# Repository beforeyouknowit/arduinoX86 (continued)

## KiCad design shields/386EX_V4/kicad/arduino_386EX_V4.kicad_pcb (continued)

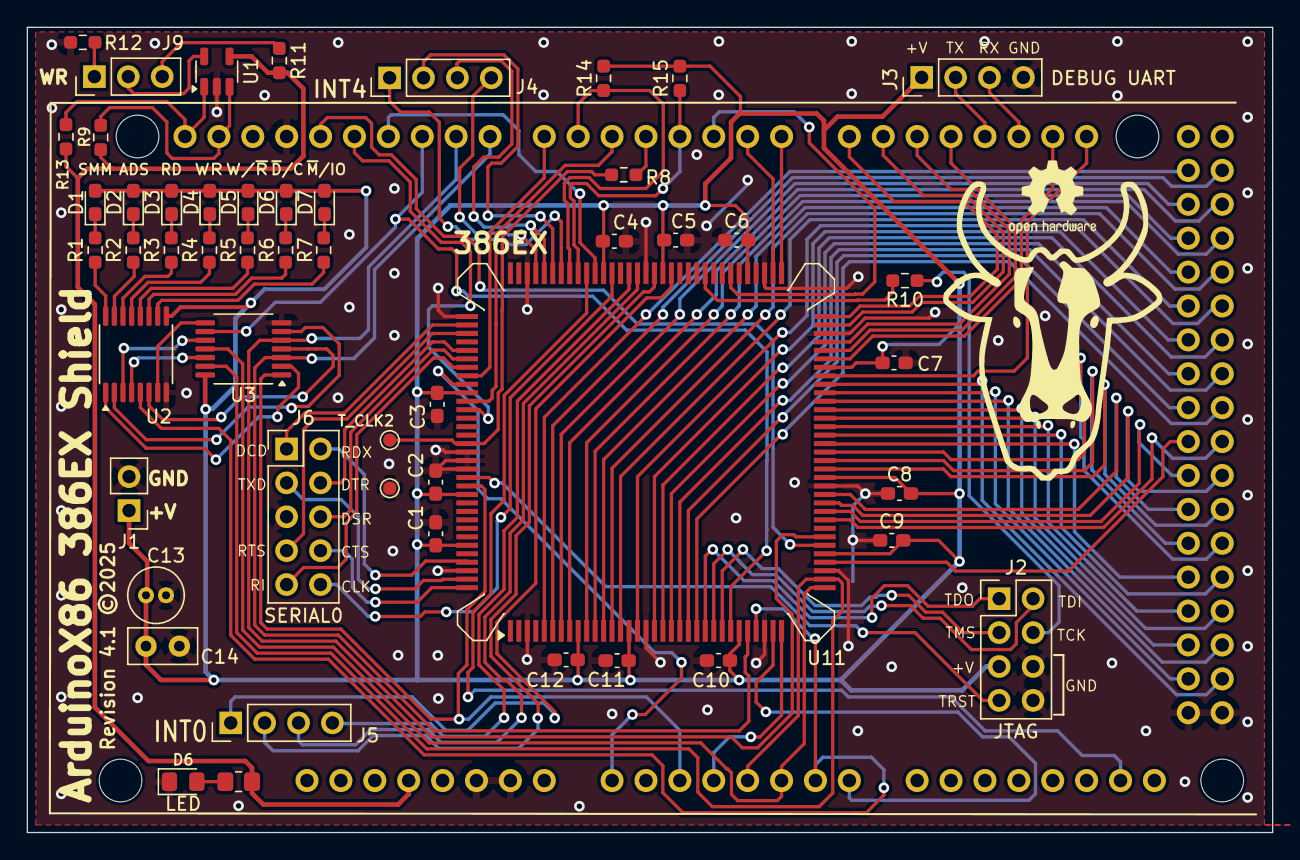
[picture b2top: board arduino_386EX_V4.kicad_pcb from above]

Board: 2 copper layers, 93.3 x 60.3 mm, 52 parts (0 on the bottom side), 115 nets.

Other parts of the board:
D6#2: LED; LED_0805_2012Metric_Pad1.15x1.40mm_HandSolder
R6#2: R_Small; R_0603_1608Metric_Pad0.98x0.95mm_HandSolder
R9, R13, R14, R15: R; R_0603_1608Metric_Pad0.98x0.95mm_HandSolder

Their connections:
GND: D6#2.1 (K); also elsewhere on the board
SCL: R13.1; also elsewhere on the board
SDA: R9.1; also elsewhere on the board
~BUSY: R14.1; also elsewhere on the board
~ERROR: R15.1; also elsewhere on the board

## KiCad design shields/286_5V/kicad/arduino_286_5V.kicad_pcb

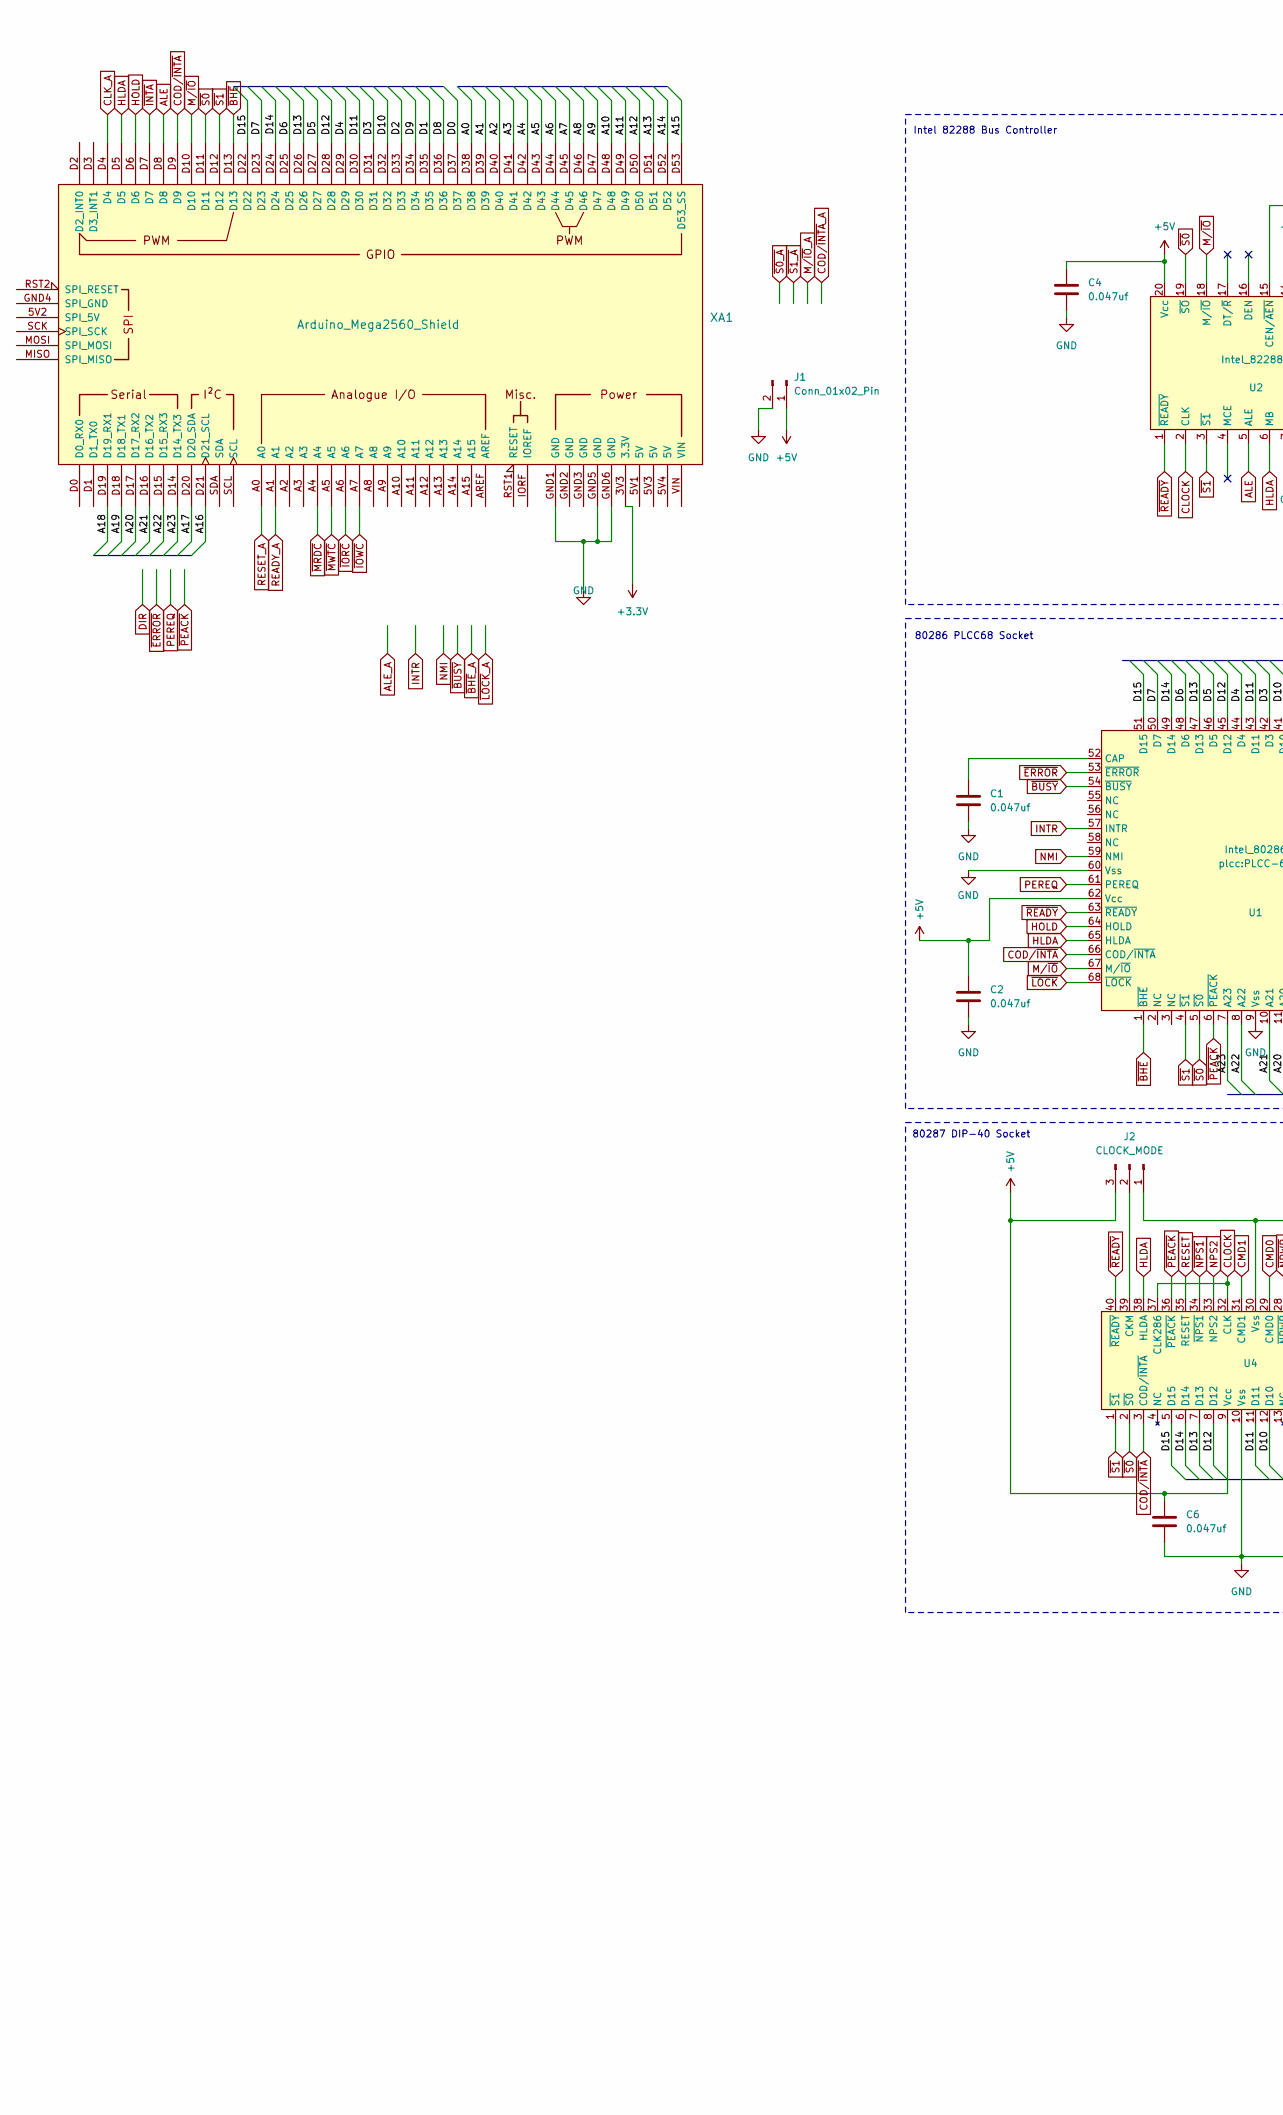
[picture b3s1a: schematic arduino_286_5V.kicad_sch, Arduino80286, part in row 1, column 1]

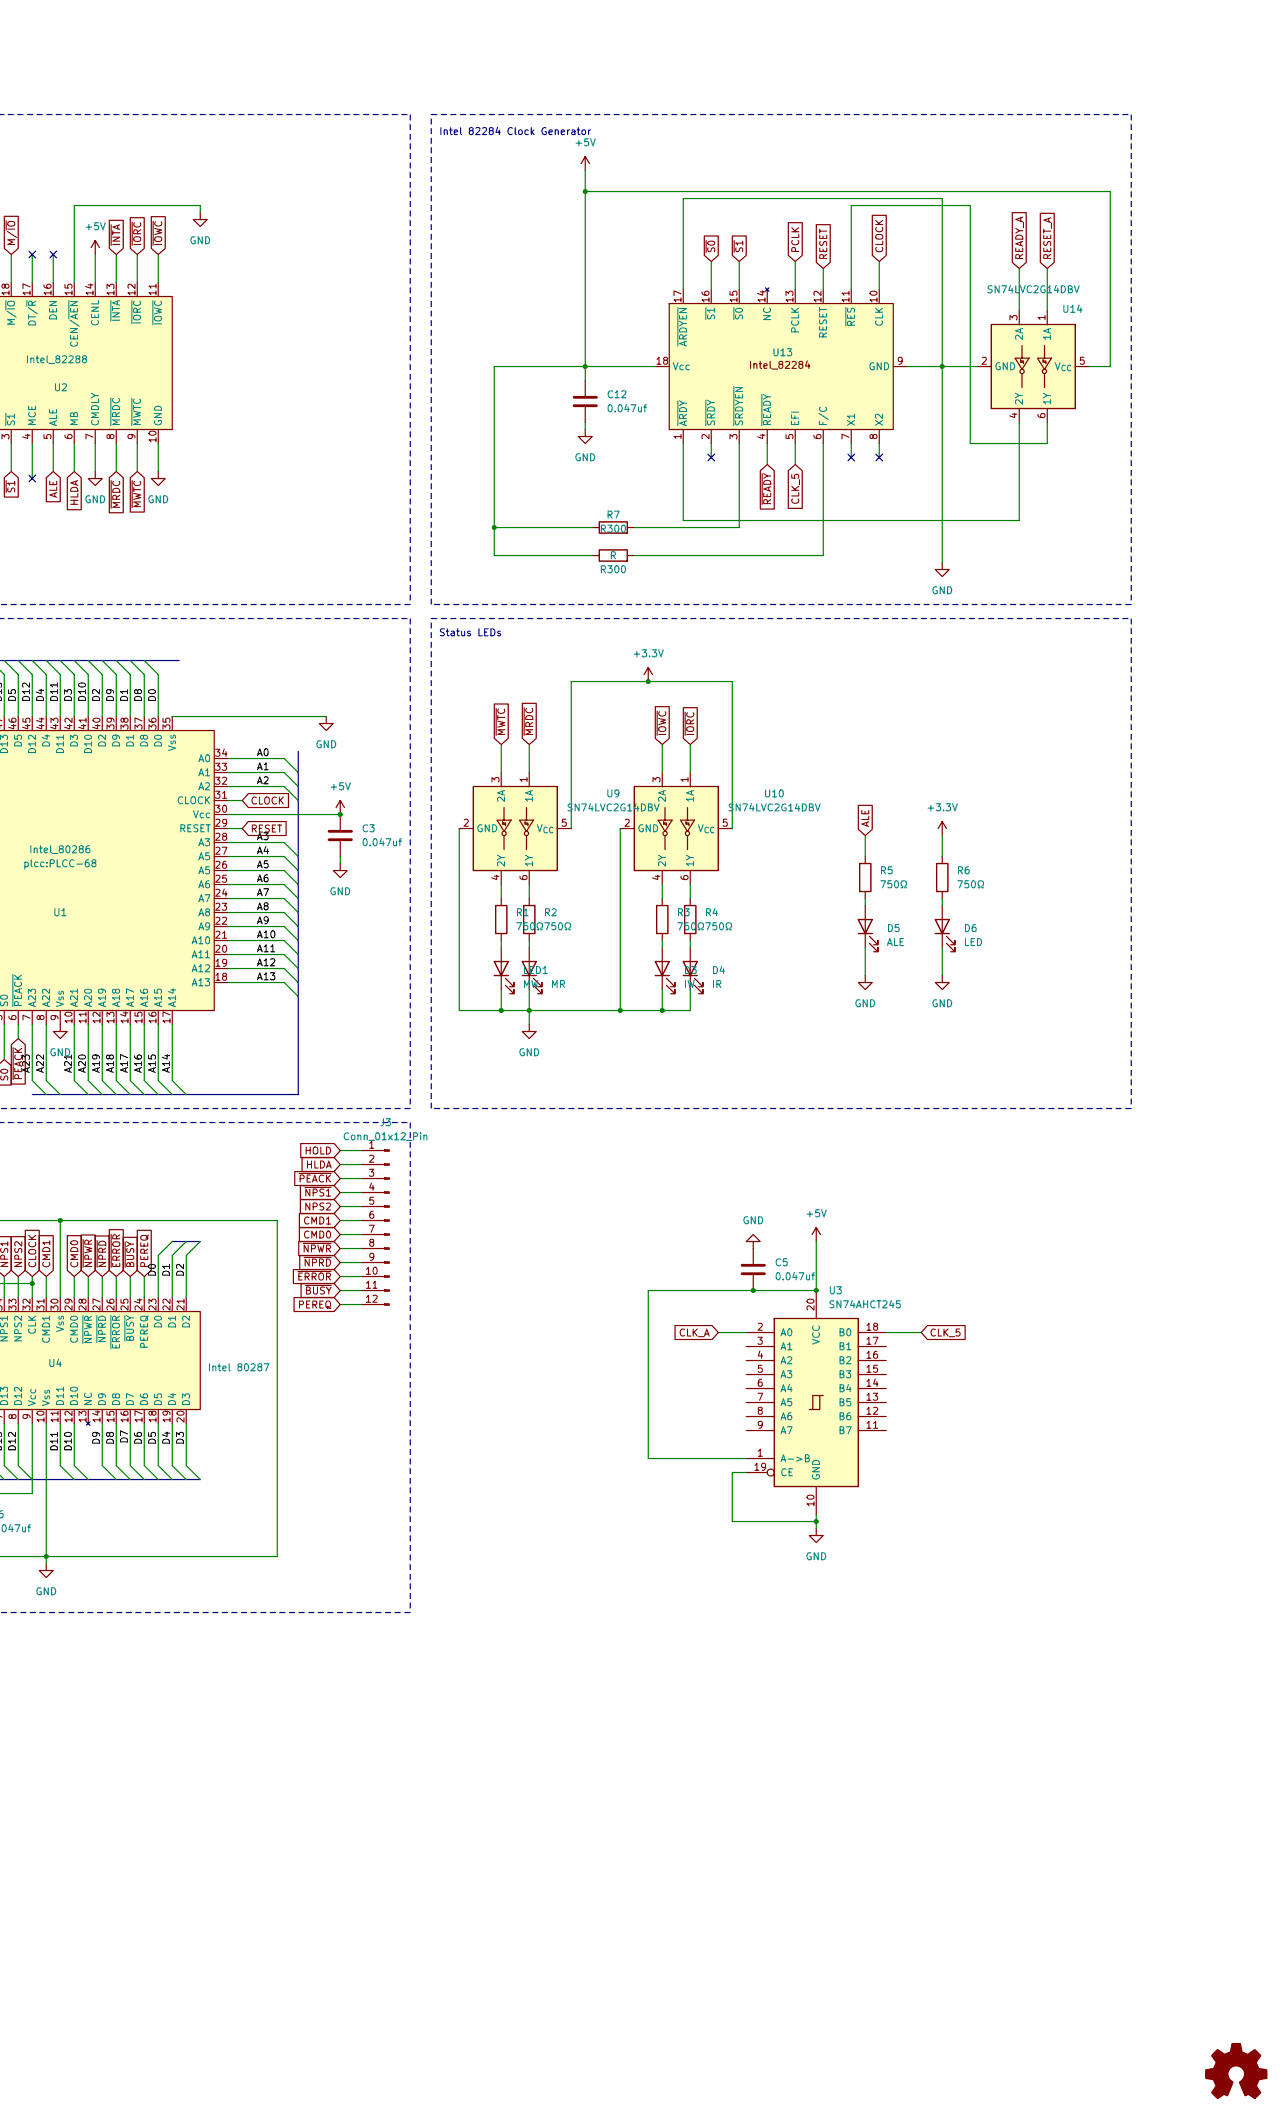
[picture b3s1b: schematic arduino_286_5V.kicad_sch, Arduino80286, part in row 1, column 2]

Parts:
C1, C2, C3, C4, C5, C6, C12: 0.047uf; C_0603_1608Metric_Pad1.08x0.95mm_HandSolder
D3: IW; LED_0805_2012Metric_Pad1.15x1.40mm_HandSolder
D4: IR; LED_0805_2012Metric_Pad1.15x1.40mm_HandSolder
D5: ALE; LED_0805_2012Metric_Pad1.15x1.40mm_HandSolder
D6: LED; LED_0805_2012Metric_Pad1.15x1.40mm_HandSolder
J1: Conn_01x02_Pin; PinHeader_1x02_P2.54mm_Horizontal
J2: CLOCK_MODE; PinHeader_1x03_P2.54mm_Vertical
J3: Conn_01x12_Pin; PinHeader_1x12_P2.54mm_Vertical
LED1: MW; LED_0805_2012Metric_Pad1.15x1.40mm_HandSolder
LED2: MR; LED_0805_2012Metric_Pad1.15x1.40mm_HandSolder
R1, R2, R3, R4, R5, R6: 750Ω; R_0805_2012Metric_Pad1.20x1.40mm_HandSolder
R7: R300; R_0805_2012Metric_Pad1.20x1.40mm_HandSolder
R300: R; R_0805_2012Metric_Pad1.20x1.40mm_HandSolder
U1: Intel_80286; PLCC-68
U2: Intel_82288; DIP-20_W7.62mm_Socket
U3: SN74AHCT245; TSSOP-20_4.4x6.5mm_P0.65mm
U4: Intel 80287; DIP-40_W15.24mm_Socket
U9, U10, U14: SN74LVC2G14DBV; SOT-23-6
U13: DIP-18_W7.62mm_Socket
XA1: Arduino_Mega2560_Shield

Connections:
+3.3V: R6.1, U9.5 (V_{CC}), U10.5 (V_{CC}), XA1.3V3 (3.3V)
+5V: C2.2, C3.2, C4.2, C5.2, C6.2, C12.2, J1.1, J2.3, R7.1, R300.1, U1.30 (Vcc), U1.62 (Vcc), U2.14 (CENL), U2.20 (Vcc), U3.1 (A->B), U3.20 (VCC), U4.9 (Vcc), U13.18 (Vcc), U14.5 (V_{CC})
/A0: U1.34 (A0), XA1.D38
/A1: U1.33 (A1), XA1.D39
/A2: U1.32 (A2), XA1.D40
/A3: U1.28 (A3), XA1.D41
/A4: U1.27 (A5), XA1.D42
/A5: U1.26 (A5), XA1.D43
/A6: U1.25 (A6), XA1.D44
/A7: U1.24 (A7), XA1.D45
/A8: U1.23 (A8), XA1.D46
/A9: U1.22 (A9), XA1.D47
/A10: U1.21 (A10), XA1.D48
/A11: U1.20 (A11), XA1.D49
/A12: U1.19 (A12), XA1.D50
/A13: U1.18 (A13), XA1.D51
/A14: U1.17 (A14), XA1.D52
/A15: U1.16 (A15), XA1.D53 (D53_SS)
/A16: U1.15 (A16), XA1.D21 (D21_SCL)
/A17: U1.14 (A17), XA1.D20 (D20_SDA)
/A18: U1.13 (A18), XA1.D19 (D19_RX1)
/A19: U1.12 (A19), XA1.D18 (D18_TX1)
/A20: U1.11 (A20), XA1.D17 (D17_RX2)
/A21: U1.10 (A21), XA1.D16 (D16_TX2)
/A22: U1.8 (A22), XA1.D15 (D15_RX3)
/A23: U1.7 (A23), XA1.D14 (D14_TX3)
/D0: U1.36 (D0), U4.23 (D0), XA1.D37
/D1: U1.38 (D1), U4.22 (D1), XA1.D35
/D2: U1.40 (D2), U4.21 (D2), XA1.D33
/D3: U1.42 (D3), U4.20 (D3), XA1.D31
/D4: U1.44 (D4), U4.19 (D4), XA1.D29
/D5: U1.46 (D5), U4.18 (D5), XA1.D27
/D6: U1.48 (D6), U4.17 (D6), XA1.D25
/D7: U1.50 (D7), U4.16 (D7), XA1.D23
/D8: U1.37 (D8), U4.15 (D8), XA1.D36
/D9: U1.39 (D9), U4.14 (D9), XA1.D34
/D10: U1.41 (D10), U4.12 (D10), XA1.D32
/D11: U1.43 (D11), U4.11 (D11), XA1.D30
/D12: U1.45 (D12), U4.8 (D12), XA1.D28
/D13: U1.47 (D13), U4.7 (D13), XA1.D26
/D14: U1.49 (D14), U4.6 (D14), XA1.D24
/D15: U1.51 (D15), U4.5 (D15), XA1.D22
ALE: R5.1, U2.5 (ALE), XA1.D8
CLK_5: U3.18 (B0), U13.5 (EFI)
CLK_A: U3.2 (A0), XA1.D4
CLOCK: U1.31 (CLOCK), U2.2 (CLK), U4.32 (CLK), U4.37 (CLK286), U13.10 (CLK)
CMD0: J3.7, U4.29 (CMD0)
CMD1: J3.6, U4.31 (CMD1)
COD/~INTA: U1.66 (COD/~INTA), U4.3 (COD/~INTA), XA1.D9
GND: C1.1, C2.1, C3.1, C4.1, C5.1, C6.1, C12.1, D3.1 (K), D4.1 (K), D5.1 (K), D6.1 (K), J1.2, J2.1, LED1.1 (K), LED2.1 (K), U1.9 (Vss), U1.35 (Vss), U1.60 (Vss), U2.7 (CMDLY), U2.10 (GND), U2.15 (CEN/~AEN), U3.10 (GND), U3.19 (CE), U4.10 (Vss), U4.30 (Vss), U9.2 (GND), U10.2 (GND), U13.9 (GND), U13.17 (~ARDYEN), U14.2 (GND), XA1.GND1 (GND), XA1.GND2 (GND), XA1.GND3 (GND), XA1.GND5 (GND), XA1.GND6 (GND)
HLDA: J3.2, U1.65 (HLDA), U2.6 (MB), U4.38 (HLDA), XA1.D5
HOLD: J3.1, U1.64 (HOLD), XA1.D6
INTR: U1.57 (INTR)
M/~IO: U1.67 (M/~IO), U2.18 (M/~IO), XA1.D10
NMI: U1.59 (NMI)
NPS2: J3.5, U4.33 (NPS2)
unnamed: D3.2 (A), R3.2
unnamed: D4.2 (A), R4.2
unnamed: D5.2 (A), R5.2
unnamed: D6.2 (A), R6.2
unnamed: J2.2, U4.39 (CKM)
unnamed: LED1.2 (A), R1.2
unnamed: LED2.2 (A), R2.2
unnamed: C1.2, U1.52 (CAP)
unnamed: R2.1, U9.6 (1Y)
unnamed: R1.1, U9.4 (2Y)
unnamed: R4.1, U10.6 (1Y)
unnamed: R3.1, U10.4 (2Y)
unnamed: R300.2, U13.6 (F/C)
unnamed: U13.1 (~ARDY), U14.4 (2Y)
unnamed: U13.11 (~RES), U14.6 (1Y)
unnamed: R7.2, U13.3 (~SRDYEN)
PCLK: U13.13 (PCLK)
PEREQ: J3.12, U1.61 (PEREQ), U4.24 (PEREQ)
READY_A: U14.3 (2A), XA1.A1
RESET: U1.29 (RESET), U4.35 (RESET), U13.12 (RESET)
RESET_A: U14.1 (1A), XA1.A0
~BHE: U1.1 (~BHE), XA1.D13
~BUSY: J3.11, U1.54 (~BUSY), U4.25 (~BUSY)
~ERROR: J3.10, U1.53 (~ERROR), U4.26 (~ERROR)
~INTA: U2.13 (~INTA), XA1.D7
~IORC: U2.12 (~IORC), U10.1 (1A), XA1.A6
~IOWC: U2.11 (~IOWC), U10.3 (2A), XA1.A7
~LOCK: U1.68 (~LOCK)
~MRDC: U2.8 (~MRDC), U9.1 (1A), XA1.A4
~MWTC: U2.9 (~MWTC), U9.3 (2A), XA1.A5
~NPRD: J3.9, U4.27 (~NPRD)
~NPS1: J3.4, U4.34 (~NPS1)
~NPWR: J3.8, U4.28 (~NPWR)
~PEACK: J3.3, U1.6 (~PEACK), U4.36 (~PEACK)
~READY: U1.63 (~READY), U2.1 (~READY), U4.40 (~READY), U13.4 (~READY)
~S0: U1.5 (~S0), U2.19 (~SO), U4.2 (~S0), U13.16 (~S1), XA1.D11
~S1: U1.4 (~S1), U2.3 (~S1), U4.1 (~S1), U13.15 (~S0), XA1.D12

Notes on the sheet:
Intel 82284 Clock Generator
Intel 82288 Bus Controller
80286 PLCC68 Socket
80287 DIP-40 Socket
Status LEDs

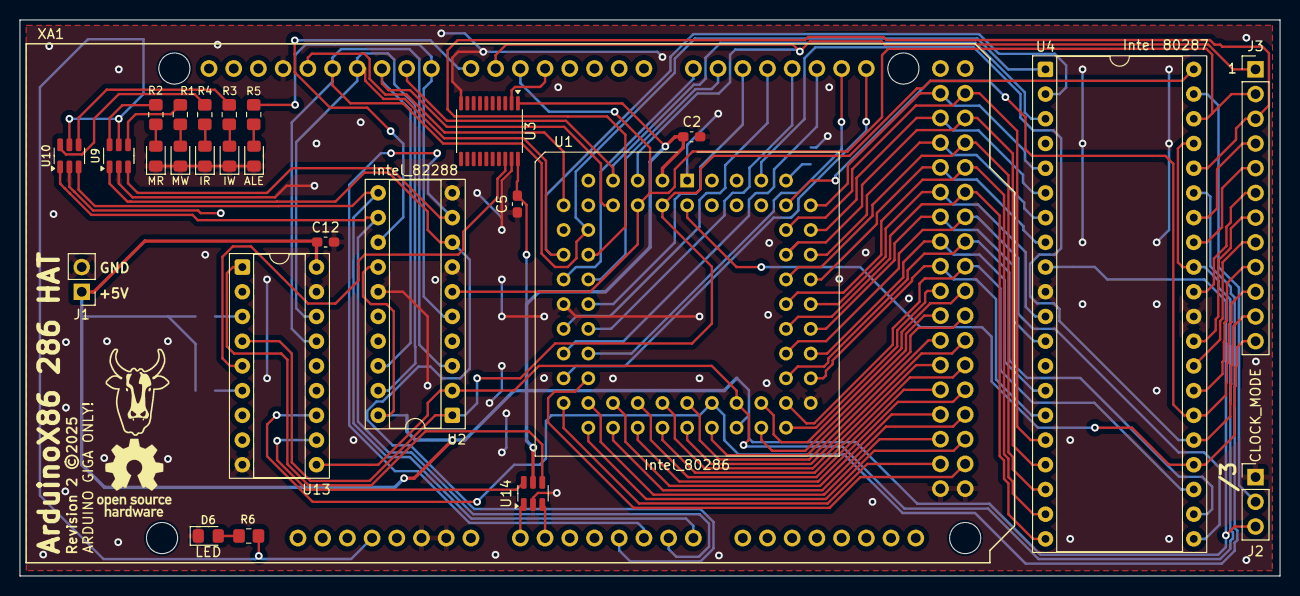
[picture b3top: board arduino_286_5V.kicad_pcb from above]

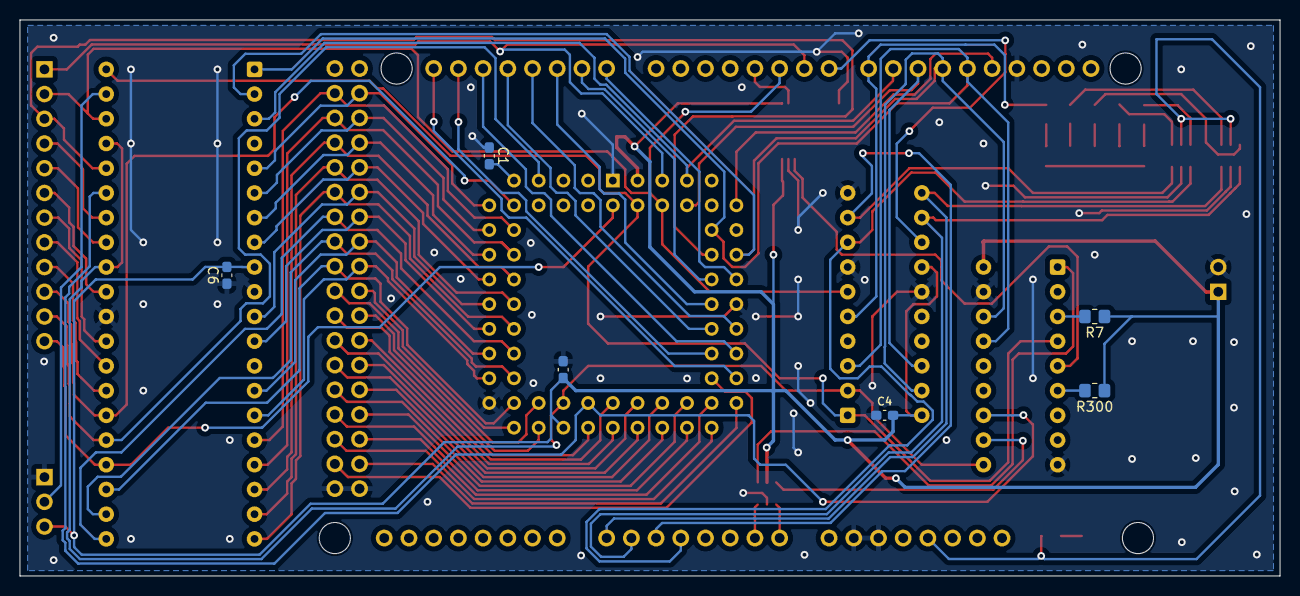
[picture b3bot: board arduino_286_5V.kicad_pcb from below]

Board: 2 copper layers, 129.5 x 57.1 mm, 33 parts (6 on the bottom side), 89 nets.

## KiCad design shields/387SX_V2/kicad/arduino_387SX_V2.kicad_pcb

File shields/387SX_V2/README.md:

## ArduinoX86 387SX Shield

This is a shield for the 387SX FPU. It is designed to be stacked on top of the 386EX V4 board.

## BOM

- This board has not been ordered and tested. I do not recommend being the first to do so!
- TBD

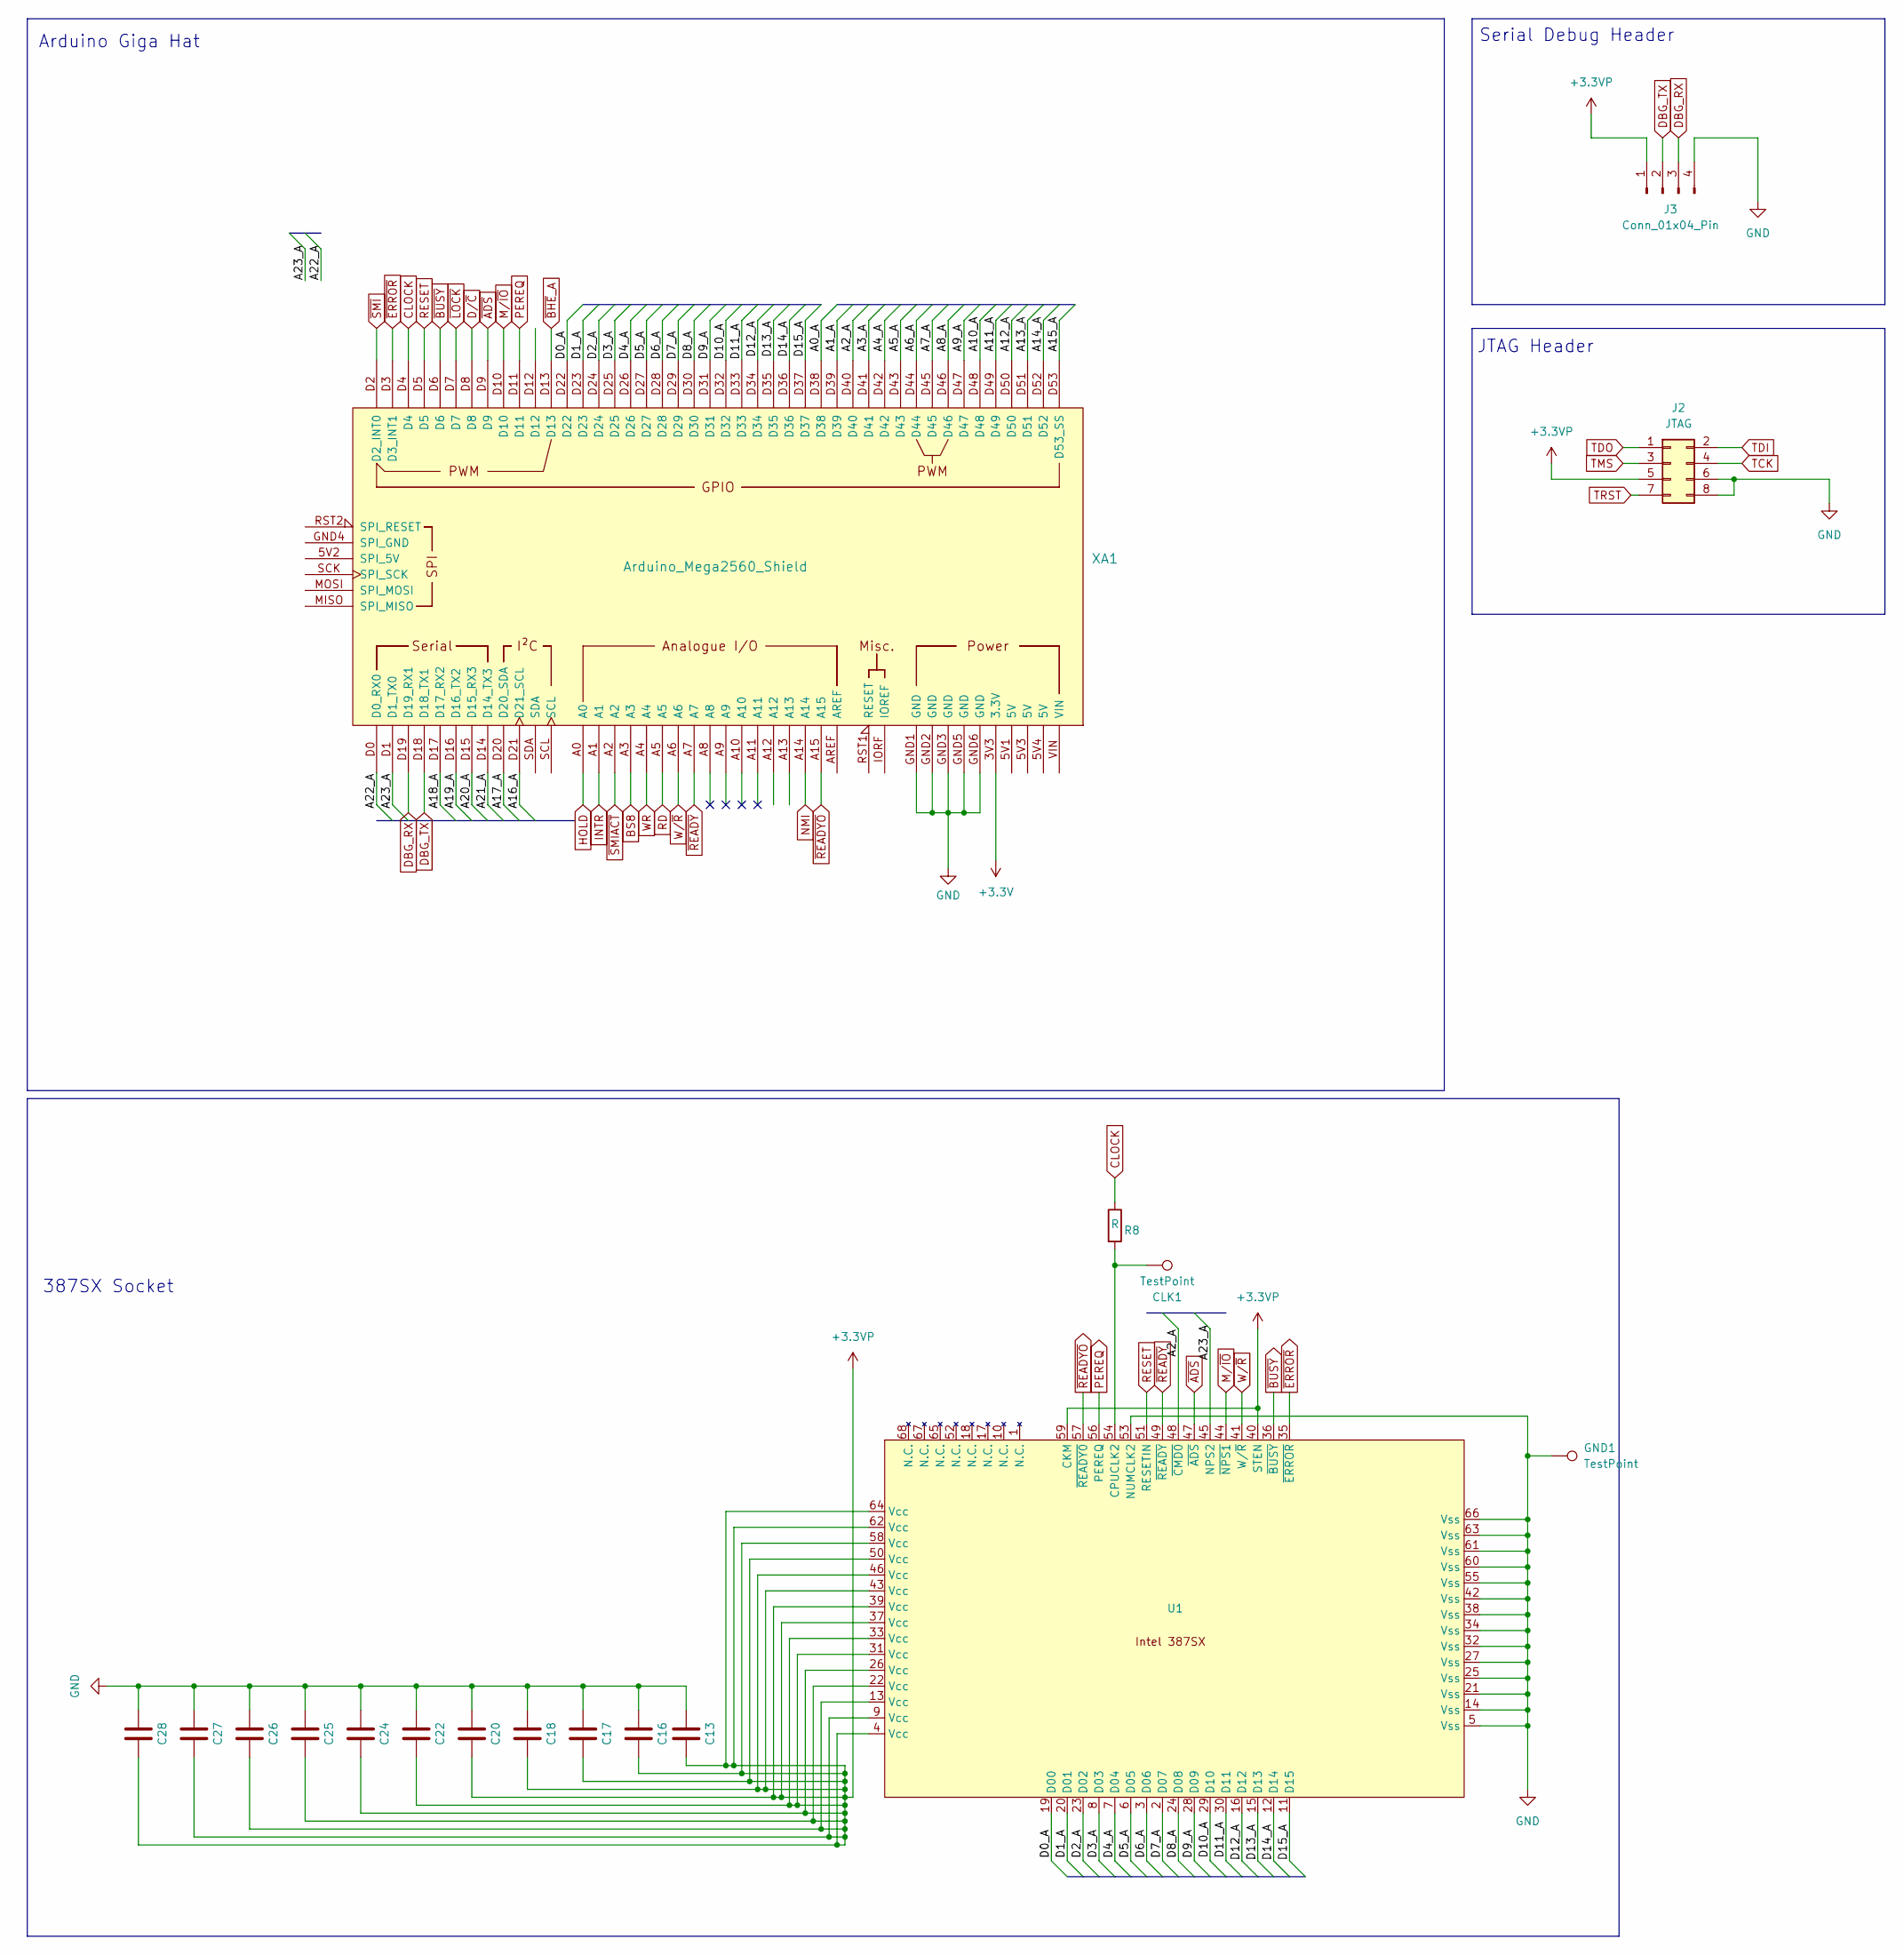
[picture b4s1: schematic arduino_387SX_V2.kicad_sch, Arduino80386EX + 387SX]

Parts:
C13, C16, C17, C18, C20, C22, C24, C25, C26, C27, C28: C; C_0603_1608Metric_Pad1.08x0.95mm_HandSolder
CLK1: TestPoint; TestPoint_Pad_D1.0mm
GND1: TestPoint; TestPoint_Pad_D1.0mm
J2: JTAG; PinSocket_2x04_P2.54mm_Vertical
J3: Conn_01x04_Pin; PinHeader_1x04_P2.54mm_Vertical
R8: R; R_0603_1608Metric_Pad0.98x0.95mm_HandSolder
U1: PLCC-68_286-THT-Socket
XA1: Arduino_Mega2560_Shield

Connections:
+3.3V: XA1.3V3 (3.3V)
+3.3VP: C13.2, C16.2, C17.2, C18.2, C20.2, C22.2, C24.2, C25.2, C26.2, C27.2, C28.2, J2.5, J3.1, U1.4 (Vcc), U1.9 (Vcc), U1.13 (Vcc), U1.22 (Vcc), U1.26 (Vcc), U1.31 (Vcc), U1.33 (Vcc), U1.37 (Vcc), U1.39 (Vcc), U1.40 (STEN), U1.43 (Vcc), U1.46 (Vcc), U1.50 (Vcc), U1.58 (Vcc), U1.59 (CKM), U1.62 (Vcc), U1.64 (Vcc)
/A0_A: XA1.D38
/A1_A: XA1.D39
/A2_A: U1.48 (~CMD0), XA1.D40
/A3_A: XA1.D41
/A4_A: XA1.D42
/A5_A: XA1.D43
/A6_A: XA1.D44
/A7_A: XA1.D45
/A8_A: XA1.D46
/A9_A: XA1.D47
/A10_A: XA1.D48
/A11_A: XA1.D49
/A12_A: XA1.D50
/A13_A: XA1.D51
/A14_A: XA1.D52
/A15_A: XA1.D53 (D53_SS)
/A16_A: XA1.D21 (D21_SCL)
/A17_A: XA1.D20 (D20_SDA)
/A18_A: XA1.D17 (D17_RX2)
/A19_A: XA1.D16 (D16_TX2)
/A20_A: XA1.D15 (D15_RX3)
/A21_A: XA1.D14 (D14_TX3)
/A22_A: XA1.D0 (D0_RX0)
/A23_A: U1.45 (NPS2), XA1.D1 (D1_TX0)
/D0_A: U1.19 (D00), XA1.D22
/D1_A: U1.20 (D01), XA1.D23
/D2_A: U1.23 (D02), XA1.D24
/D3_A: U1.8 (D03), XA1.D25
/D4_A: U1.7 (D04), XA1.D26
/D5_A: U1.6 (D05), XA1.D27
/D6_A: U1.3 (D06), XA1.D28
/D7_A: U1.2 (D07), XA1.D29
/D8_A: U1.24 (D08), XA1.D30
/D9_A: U1.28 (D09), XA1.D31
/D10_A: U1.29 (D10), XA1.D32
/D11_A: U1.30 (D11), XA1.D33
/D12_A: U1.16 (D12), XA1.D34
/D13_A: U1.15 (D13), XA1.D35
/D14_A: U1.12 (D14), XA1.D36
/D15_A: U1.11 (D15), XA1.D37
BS8: XA1.A3
CLOCK: R8.1, XA1.D4
DBG_RX: J3.3, XA1.D19 (D19_RX1)
DBG_TX: J3.2, XA1.D18 (D18_TX1)
D/~C: XA1.D8
GND: C13.1, C16.1, C17.1, C18.1, C20.1, C22.1, C24.1, C25.1, C26.1, C27.1, C28.1, GND1.1, J2.6, J2.8, J3.4, U1.5 (Vss), U1.14 (Vss), U1.21 (Vss), U1.25 (Vss), U1.27 (Vss), U1.32 (Vss), U1.34 (Vss), U1.38 (Vss), U1.42 (Vss), U1.53 (NUMCLK2), U1.55 (Vss), U1.60 (Vss), U1.61 (Vss), U1.63 (Vss), U1.66 (Vss), XA1.GND1 (GND), XA1.GND2 (GND), XA1.GND3 (GND), XA1.GND5 (GND), XA1.GND6 (GND)
HOLD: XA1.A0
INTR: XA1.A1
M/~IO: U1.44 (~NPS1), XA1.D10
NMI: XA1.A14
unnamed: CLK1.1, R8.2, U1.54 (CPUCLK2)
PEREQ: U1.56 (PEREQ), XA1.D11
RD: XA1.A5
RESET: U1.51 (RESETIN), XA1.D5
TCK: J2.4
TDI: J2.2
TDO: J2.1
TMS: J2.3
TRST: J2.7
WR: XA1.A4
W/~R: U1.41 (W/~R), XA1.A6
~ADS: U1.47 (~ADS), XA1.D9
~BUSY: U1.36 (~BUSY), XA1.D6
~ERROR: U1.35 (~ERROR), XA1.D3 (D3_INT1)
~LOCK: XA1.D7
~READYO: U1.57 (~READY0), XA1.A15
~READY: U1.49 (~READY), XA1.A7
~SMIACT: XA1.A2
~SMI: XA1.D2 (D2_INT0)

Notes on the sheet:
JTAG Header
Serial Debug Header
387SX Socket
Arduino Giga Hat

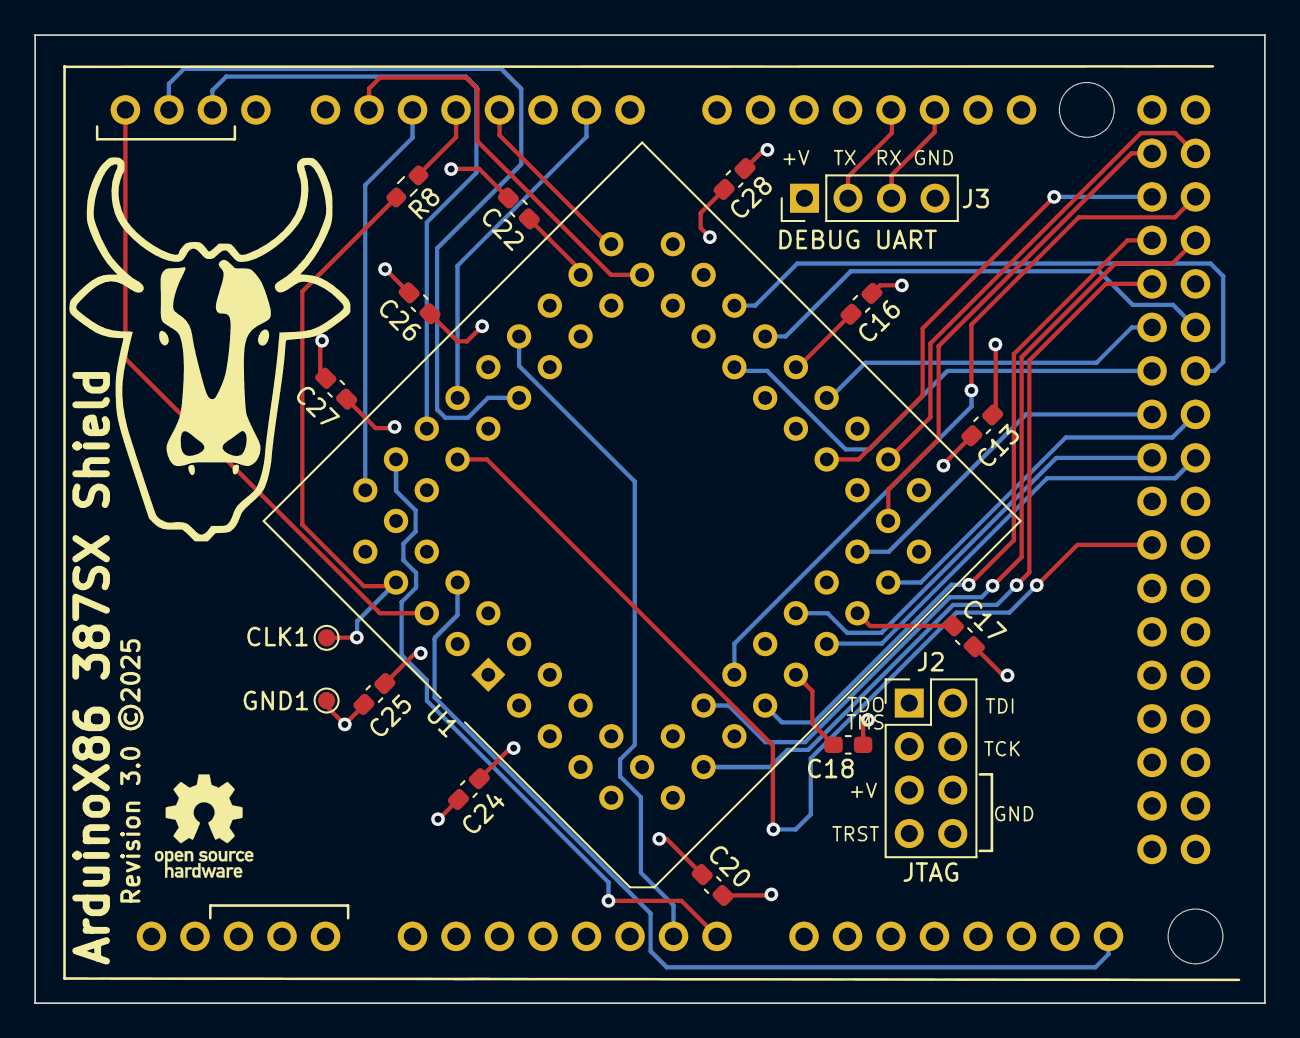
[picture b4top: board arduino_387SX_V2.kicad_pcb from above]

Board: 4 copper layers, 71.8 x 56.5 mm, 18 parts (0 on the bottom side), 33 nets.

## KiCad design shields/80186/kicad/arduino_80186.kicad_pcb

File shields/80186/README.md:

## ArduinoX86 8018X Shield

This will eventually be a shield for the 80186. It is still being designed.

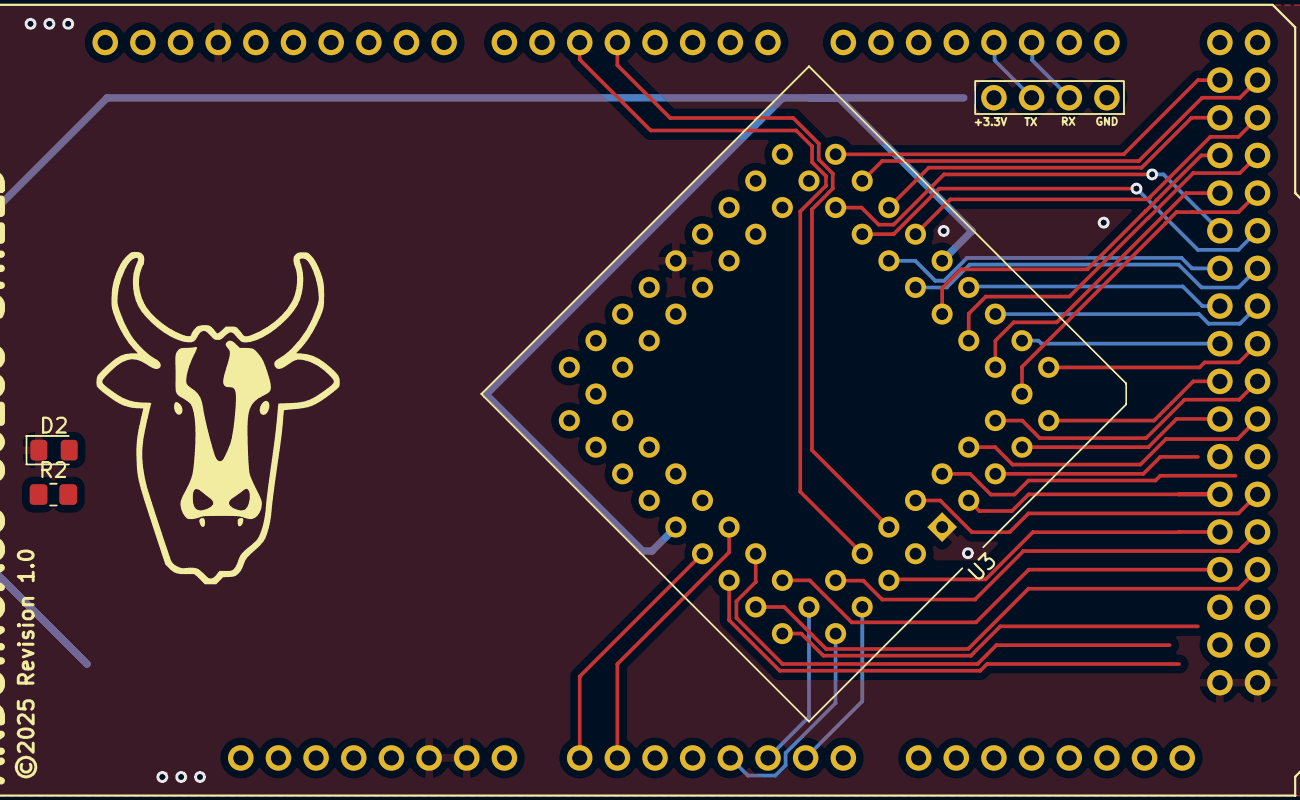
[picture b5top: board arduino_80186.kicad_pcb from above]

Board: 2 copper layers, 4 parts (0 on the bottom side), 41 nets.

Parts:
D2: LED; LED_0805_2012Metric_Pad1.15x1.40mm_HandSolder
R2: 750Ω; R_0805_2012Metric_Pad1.20x1.40mm_HandSolder
U3: 80186; PLCC-68_286-THT-Socket
XA1: Arduino_Mega2560_Shield

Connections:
+3.3V: R2.1, U3.9 (VCC), U3.43 (VCC), XA1.3V3 (3.3V)
+5V: XA1.5V3 (5V), XA1.5V4 (5V)
/A8: U3.16 (AD8), XA1.D30
/A9: U3.14 (AD9), XA1.D31
/A10: U3.12 (AD10), XA1.D32
/A11: U3.10 (AD11), XA1.D33
/A12: U3.7 (AD12), XA1.D34
/A13: U3.5 (AD13), XA1.D35
/A14: U3.3 (AD14), XA1.D36
/A15: U3.1 (AD15), XA1.D37
/A16: U3.68 (A16/S3), XA1.D38
/A17: U3.67 (A17/S4), XA1.D39
/A18: U3.66 (A18/S5), XA1.D40
/A19: U3.65 (A19/S6), XA1.D41
/AD0: U3.17 (AD0), XA1.D22
/AD1: U3.15 (AD1), XA1.D23
/AD2: U3.13 (AD2), XA1.D24
/AD3: U3.11 (AD3), XA1.D25
/AD4: U3.8 (AD4), XA1.D26
/AD5: U3.6 (AD5), XA1.D27
/AD6: U3.4 (AD6), XA1.D28
/AD7: U3.2 (AD7), XA1.D29
/CLK: U3.59 (X1), XA1.D4
/INTR: U3.45 (INT0), XA1.A0, XA1.D12
/NMI: U3.46 (NMI), XA1.A1, XA1.D13
/~LOCK: U3.48 (~LOCK), XA1.D10
/~S0: U3.52 (~S0), XA1.A4
/~S1: U3.53 (~S1), XA1.A5
/~S2: U3.54 (~S2), XA1.A6
/~TEST: U3.47 (~TEST), XA1.D7
AREADY: U3.55 (ARDY), XA1.D47
CLKOUT: U3.56 (CLKOUT), XA1.D46
GND: D2.1 (K), U3.26 (VSS), U3.60 (VSS), XA1.GND1 (GND), XA1.GND2 (GND), XA1.GND3 (GND), XA1.GND5 (GND), XA1.GND6 (GND)
HOLD: U3.50 (HOLD), XA1.D48
unnamed: D2.2 (A), R2.2
QS0: U3.61 (ALE/QS0), XA1.D8, XA1.D45
QS1: U3.63 (~WR/QS1), XA1.D9, XA1.D43
RESET: U3.57 (RESET), XA1.D5
SREADY: U3.49 (SRDY), XA1.D49
~BHE/S7: U3.64 (~BHE/S7), XA1.D42
~RD\~QSMD: U3.62 (~RD/~QSMD), XA1.D44
